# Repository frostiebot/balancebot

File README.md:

# balancebot

### VERY MUCH WIP

Semi-Clean-Room attempt at a self-balancing robot powered by an ESP32 + 2 DRV8825 StepSticks.

Includes schematics in KiCAD format.

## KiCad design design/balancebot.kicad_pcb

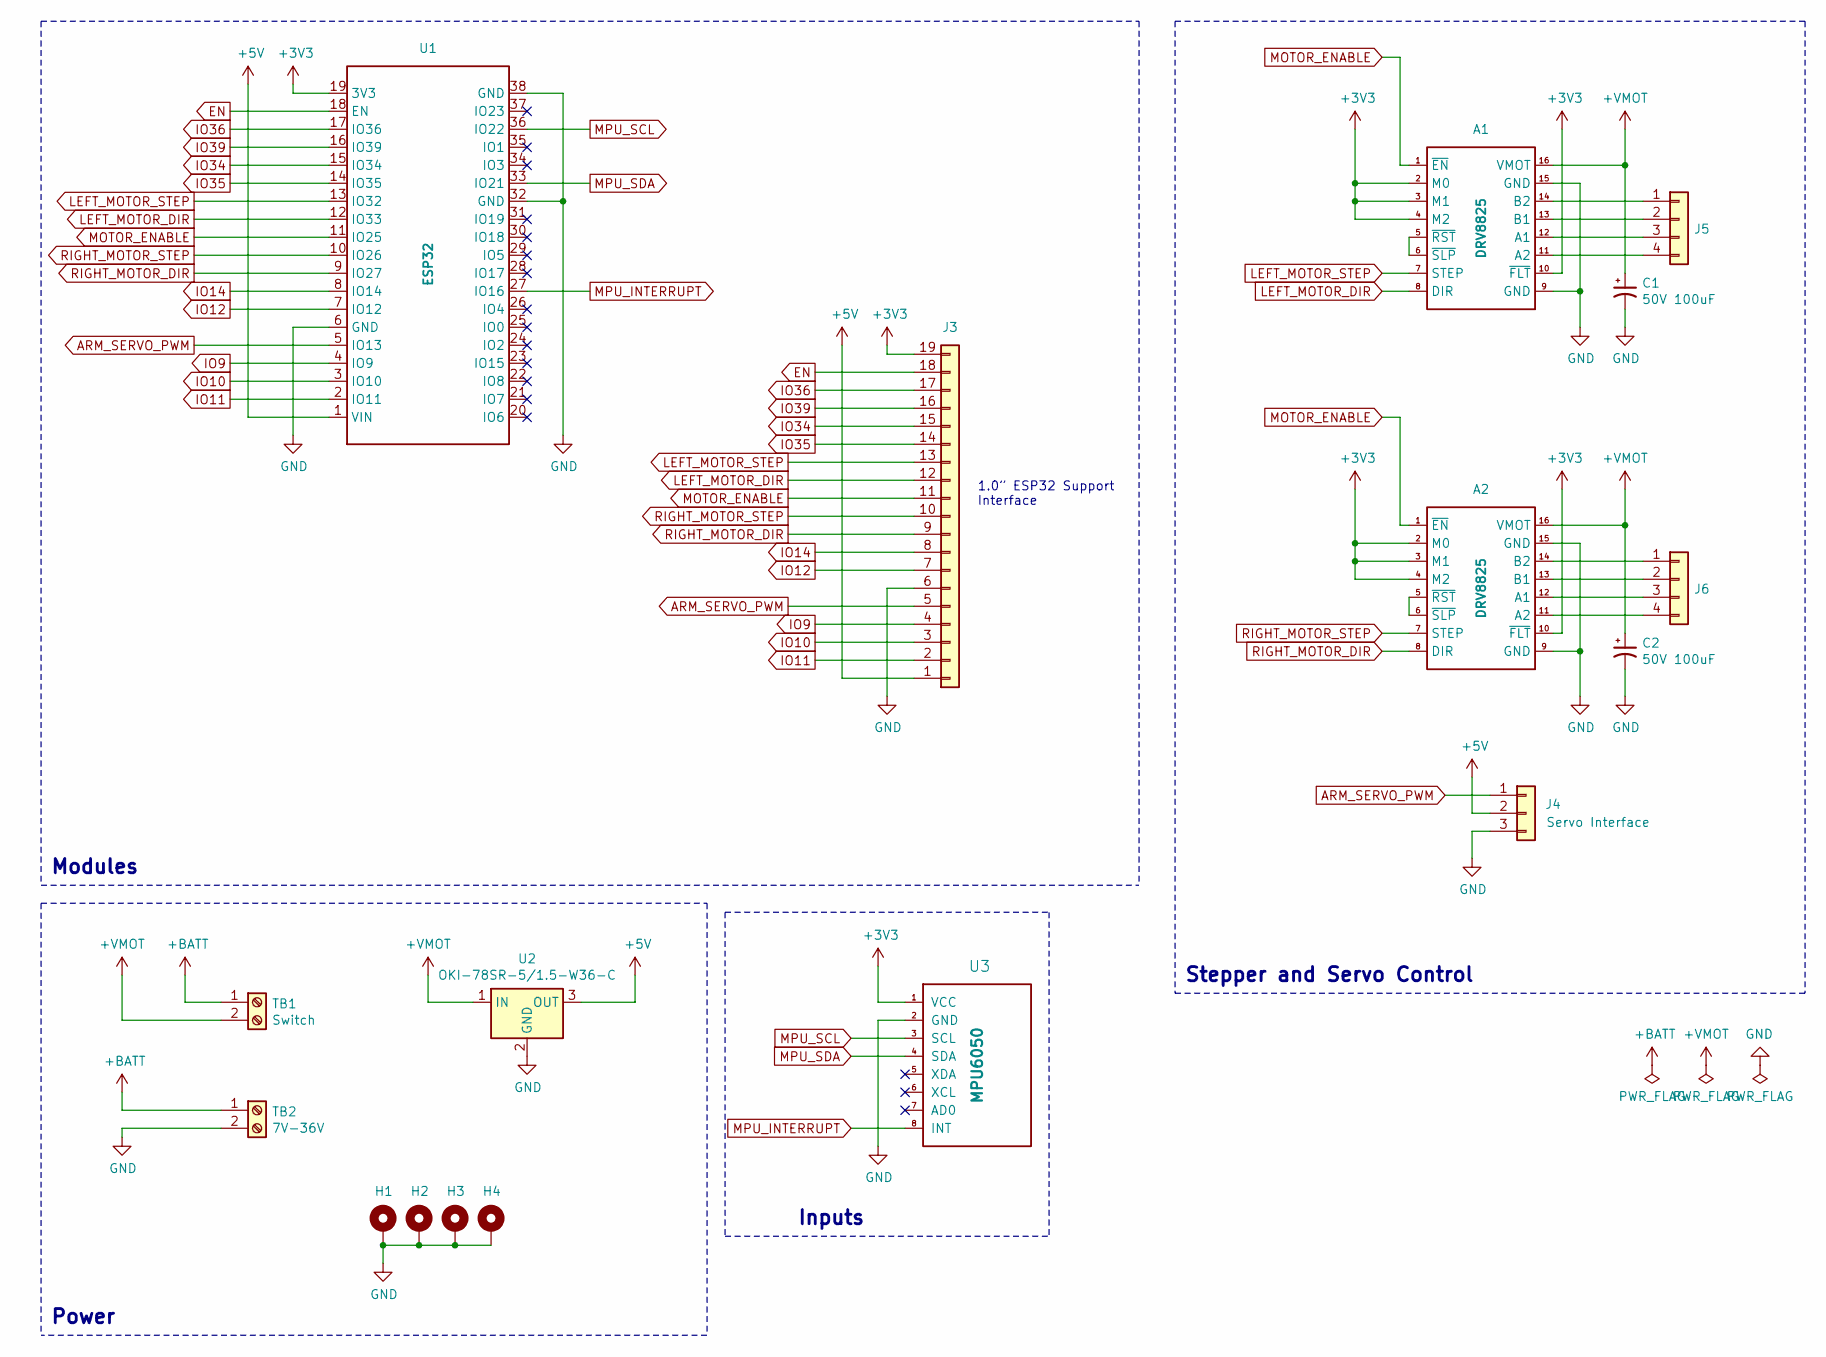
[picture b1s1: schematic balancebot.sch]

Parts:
A1, A2: DRV8825; bb_Pololu_Breakout-16_15.2x20.3mm
C1, C2: 50V 100uF; bb_C_Rect_L7.0mm_W2.5mm_P5.00mm
H1, H2, H3, H4: MountingHole_Pad; MountingHole_2.2mm_M2
J3: Passthrough; bb_PinSocket_1x19_P2.54mm_Vertical
J4: Servo Interface; PinHeader_1x03_P2.54mm_Vertical
J5: Left Motor Interface; PinHeader_1x04_P2.54mm_Vertical
J6: Right Motor Interface; PinHeader_1x04_P2.54mm_Vertical
TB1: Switch; bb_TE_282837-2
TB2: 7V-36V; bb_TE_282837-2
U1: ESP32; bb_ESP32-DEVKITC
U2: OKI-78SR-5/1.5-W36-C; Converter_DCDC_muRata_OKI-78SR_Vertical
U3: MPU6050; bb_GY-521

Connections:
+3V3: A1.2 (M0), A1.3 (M1), A1.4 (M2), A1.10 (~FLT), A2.2 (M0), A2.3 (M1), A2.4 (M2), A2.10 (~FLT), J3.19, U1.19 (3V3), U3.1 (VCC)
+5V: J3.1, J4.2, U1.1 (VIN), U2.3 (OUT)
+BATT: TB1.1, TB2.1
+VMOT: A1.16 (VMOT), A2.16 (VMOT), C1.1, C2.1, TB1.2, U2.1 (IN)
ARM_SERVO_PWM: J3.5, J4.1, U1.5 (IO13)
EN: J3.18, U1.18 (EN)
GND: A1.9 (GND), A1.15 (GND), A2.9 (GND), A2.15 (GND), C1.2, C2.2, H1.1, H2.1, H3.1, H4.1, J3.6, J4.3, TB2.2, U1.6 (GND), U1.32 (GND), U1.38 (GND), U2.2 (GND), U3.2 (GND)
IO9: J3.4, U1.4 (IO9)
IO10: J3.3, U1.3 (IO10)
IO11: J3.2, U1.2 (IO11)
IO12: J3.7, U1.7 (IO12)
IO14: J3.8, U1.8 (IO14)
IO34: J3.15, U1.15 (IO34)
IO35: J3.14, U1.14 (IO35)
IO36: J3.17, U1.17 (IO36)
IO39: J3.16, U1.16 (IO39)
LEFT_MOTOR_DIR: A1.8 (DIR), J3.12, U1.12 (IO33)
LEFT_MOTOR_STEP: A1.7 (STEP), J3.13, U1.13 (IO32)
MOTOR_ENABLE: A1.1 (~EN), A2.1 (~EN), J3.11, U1.11 (IO25)
MPU_INTERRUPT: U1.27 (IO16), U3.8 (INT)
MPU_SCL: U1.36 (IO22), U3.3 (SCL)
MPU_SDA: U1.33 (IO21), U3.4 (SDA)
unnamed: A1.5 (~RST), A1.6 (~SLP)
unnamed: A1.11 (A2), J5.4
unnamed: A1.12 (A1), J5.3
unnamed: A1.13 (B1), J5.2
unnamed: A1.14 (B2), J5.1
unnamed: A2.5 (~RST), A2.6 (~SLP)
unnamed: A2.11 (A2), J6.4
unnamed: A2.12 (A1), J6.3
unnamed: A2.13 (B1), J6.2
unnamed: A2.14 (B2), J6.1
RIGHT_MOTOR_DIR: A2.8 (DIR), J3.9, U1.9 (IO27)
RIGHT_MOTOR_STEP: A2.7 (STEP), J3.10, U1.10 (IO26)

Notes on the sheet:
Stepper and Servo Control
Power
Inputs
Modules
1.0” ESP32 Support Interface

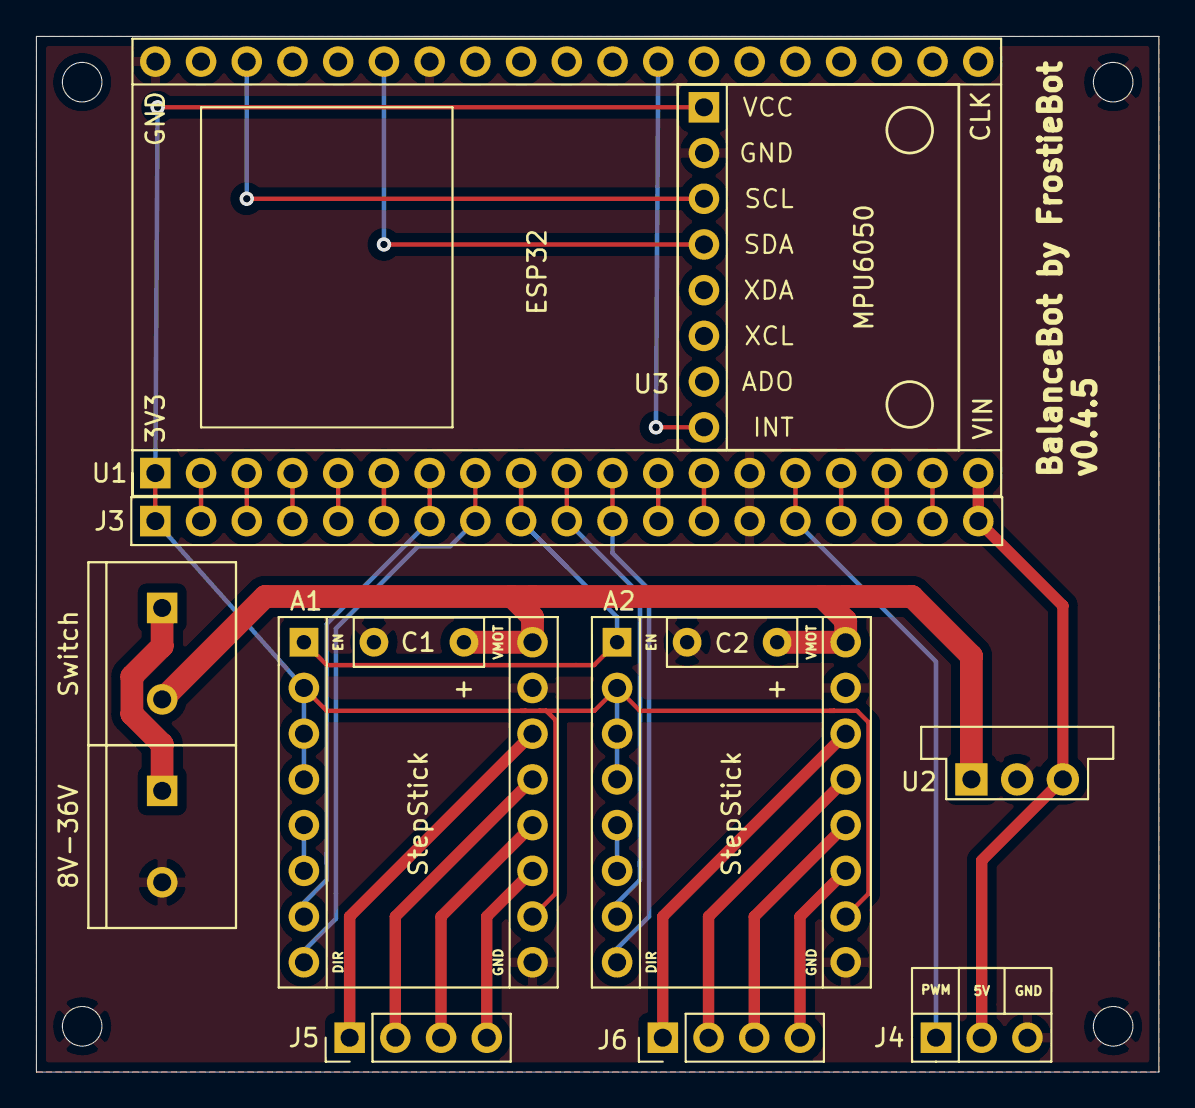
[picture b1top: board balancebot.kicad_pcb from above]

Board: 2 copper layers, 62.4 x 57.5 mm, 17 parts (0 on the bottom side), 34 nets.

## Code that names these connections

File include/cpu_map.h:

#ifndef CPU_MAP_H
#define CPU_MAP_H

#define STEPPER_ENABLE_PIN        GPIO_NUM_27

#define STEPPER_LEFT_STEP_PIN     GPIO_NUM_32
#define STEPPER_LEFT_DIR_PIN      GPIO_NUM_33

#define STEPPER_RIGHT_STEP_PIN    GPIO_NUM_25
#define STEPPER_RIGHT_DIR_PIN     GPIO_NUM_26

#define SERVO_PWM_PIN             GPIO_NUM_17

#define MPU_SCL_PIN               GPIO_NUM_22
#define MPU_SDA_PIN               GPIO_NUM_21
#define MPU_INTERRUPT_PIN         GPIO_NUM_16

#endif

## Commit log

2019-11-07 WIP haphazard and lazy integration of MPU6050 + PID library code
2019-11-18 WIP PCB design update
2019-11-19 added evaluation code + fixes for Simple_MPU6050
2019-11-21 update IMU control code to use interrupts. other QoL changes
2019-11-26 more WIP additions. steppers now work, albeit a little weirdly.
